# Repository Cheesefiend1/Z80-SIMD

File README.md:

# Z80-SIMD

The first (maybe only ever) SIMD z80 computer.
Software will be written soon

Schematics in PDF form are available aswell in kicad schematic form.

Go nuts!

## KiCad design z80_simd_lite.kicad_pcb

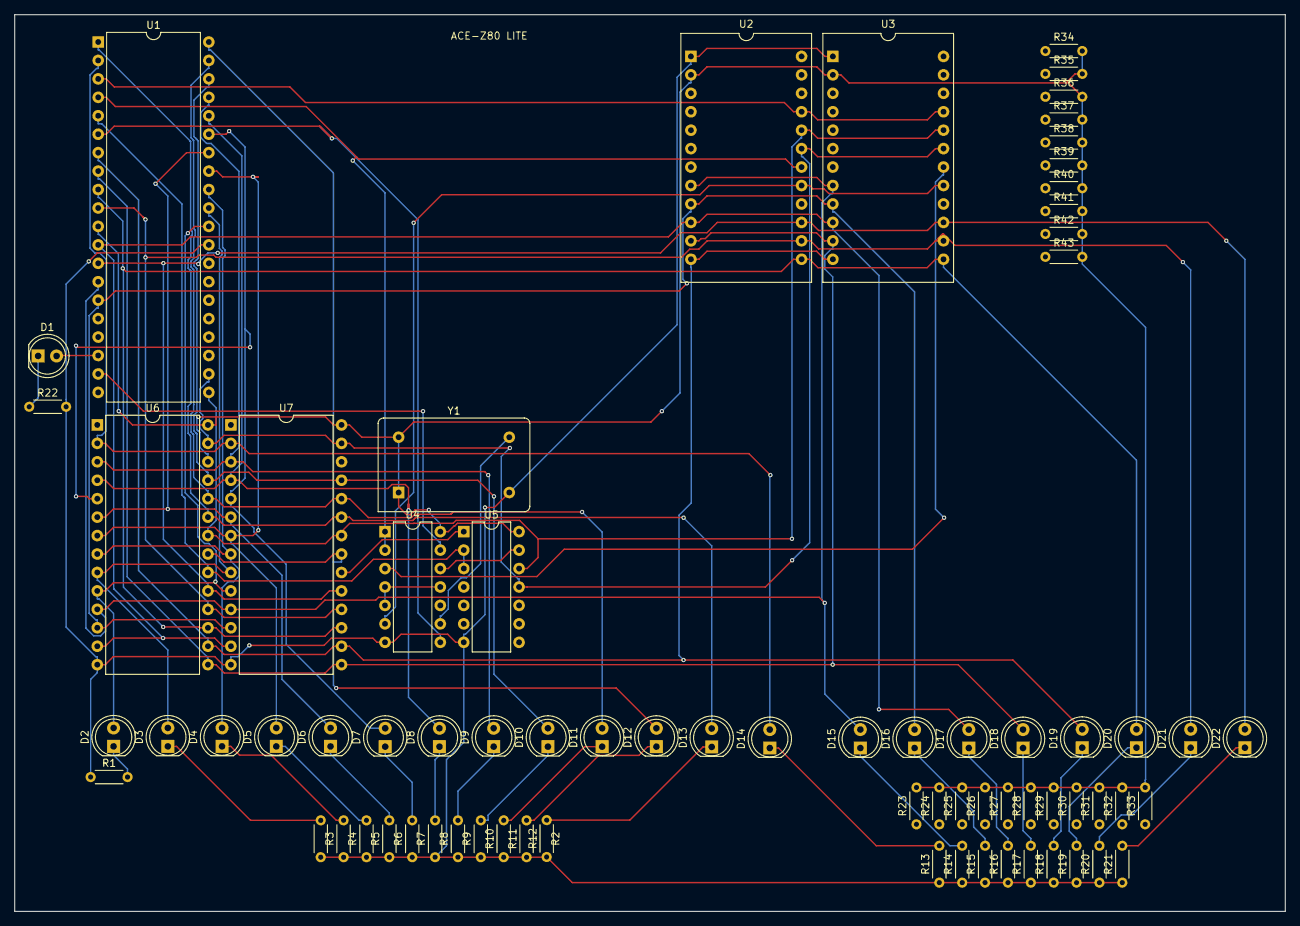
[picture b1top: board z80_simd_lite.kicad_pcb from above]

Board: 2 copper layers, 175.0 x 123.5 mm, 73 parts (0 on the bottom side), 59 nets.

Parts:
D1, D2, D3, D4, D5, D6, D7, D8, D9, D10, D11, D12, D13, D14, D15, D16, D17, D18, D19, D20, D21, D22: LED; LED_D5.0mm
R1, R2, R3, R4, R5, R6, R7, R8, R9, R10, R11, R12, R13, R14, R15, R16, R17, R18, R19, R20, R21, R22, R23, R24, R25, R26, R27, R28, R29, R30, R31, R32, R33, R34, R35, R36, R37, R38, R39, R40, R41, R42, R43: R; R_Axial_DIN0204_L3.6mm_D1.6mm_P5.08mm_Horizontal
U1: Z80CPU; DIP-40_W15.24mm
U2, U3: DIP-24_18.0mmx34.29mm_W15.24mm
U4: 74LS00; DIP-14_W7.62mm
U5: 7402; DIP-14_W7.62mm
U6: HY6264AxP; DIP-28_W15.24mm
U7: KM28C64A; DIP-28_W15.24mm
Y1: CXO_DIP14; Oscillator_DIP-14

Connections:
/A0: D2.2 (A), U1.30 (A0), U6.10 (A0), U7.10 (A0)
/A1: D3.2 (A), U1.31 (A1), U6.9 (A1), U7.9 (A1)
/A2: D4.2 (A), U1.32 (A2), U6.8 (A2), U7.8 (A2)
/A3: D5.2 (A), U1.33 (A3), U6.7 (A3), U7.7 (A3)
/A4: D6.2 (A), U1.34 (A4), U6.6 (A4), U7.6 (A4)
/A5: D7.2 (A), U1.35 (A5), U6.5 (A5), U7.5 (A5)
/A6: D8.2 (A), U1.36 (A6), U6.4 (A6), U7.4 (A6)
/A7: D9.2 (A), U1.37 (A7), U6.3 (A7), U7.3 (A7)
/A8: D10.2 (A), U1.38 (A8), U6.25 (A8), U7.25 (A8)
/A9: D11.2 (A), U1.39 (A9), U6.24 (A9), U7.24 (A9)
/A10: D12.2 (A), U1.40 (A10), U6.21 (A10), U7.21 (A10)
/A11: D13.2 (A), U1.1 (A11), U6.23 (A11), U7.23 (A11)
/A12: D14.2 (A), U1.2 (A12), U6.2 (A12), U7.2 (A12)
/D0: D15.2 (A), U1.14 (D0), U2.8 (DB0), U3.8 (DB0), U6.11 (I/O0), U7.11 (I/O0)
/D1: D16.2 (A), U1.15 (D1), U2.9 (DB1), U3.9 (DB1), U6.12 (I/O1), U7.12 (I/O1)
/D2: D17.2 (A), U1.12 (D2), U2.10 (DB2), U3.10 (DB2), U6.13 (I/O2), U7.13 (I/O2)
/D3: D18.2 (A), U1.8 (D3), U2.11 (DB3), U3.11 (DB3), U6.15 (I/O3), U7.15 (I/O3)
/D4: D19.2 (A), U1.7 (D4), U2.12 (DB4), U3.12 (DB4), U6.16 (I/O4), U7.16 (I/O4)
/D5: D20.2 (A), U1.9 (D5), U2.13 (DB5), U3.13 (DB5), U6.17 (I/O5), U7.17 (I/O5)
/D6: D21.2 (A), U1.10 (D6), U2.14 (DB6), U3.14 (DB6), U6.18 (I/O6), U7.18 (I/O6)
/D7: D22.2 (A), U1.13 (D7), U2.15 (DB7), U3.15 (DB7), U6.19 (I/O7), U7.19 (I/O7)
unnamed: D1.2 (A), U1.18 (~HALT)
unnamed: D1.1 (K), R22.1
unnamed: D2.1 (K), R1.2
unnamed: D3.1 (K), R2.2
unnamed: D4.1 (K), R3.2
unnamed: D5.1 (K), R4.2
unnamed: D6.1 (K), R5.2
unnamed: D7.1 (K), R6.2
unnamed: D8.1 (K), R7.2
unnamed: D9.1 (K), R8.2
unnamed: D10.1 (K), R9.2
unnamed: D11.1 (K), R10.2
unnamed: D12.1 (K), R11.2
unnamed: D13.1 (K), R12.2
unnamed: D14.1 (K), R13.2
unnamed: D15.1 (K), R14.2
unnamed: D16.1 (K), R15.2
unnamed: D17.1 (K), R16.2
unnamed: D18.1 (K), R17.2
unnamed: D19.1 (K), R18.2
unnamed: D20.1 (K), R19.2
unnamed: D21.1 (K), R20.2
unnamed: D22.1 (K), R21.2
unnamed: U1.3 (A13), U2.21 (C/D), U3.21 (C/D)
unnamed: U1.4 (A14), U2.18 (CS), U4.1, U4.2
unnamed: U1.5 (A15), U5.2, U5.3, U6.20 (~CS1)
unnamed: R1.1, R2.1, R3.1, R4.1, R5.1, R6.1, R7.1, R8.1, R9.1, R10.1, R11.1, R12.1, R13.1, R14.1, R15.1, R16.1, R17.1, R18.1, R19.1, R20.1, R21.1, R22.2, U1.29 (GND), U2.1 (VSS), U3.1 (VSS), U4.7 (GND), U5.7 (GND), U6.14 (GND), U7.14 (GND), Y1.7 (GND)
unnamed: R23.2, R24.2, R25.2, R26.2, R27.2, R28.2, R29.2, R30.2, R31.2, R32.2, R33.2, R34.2, R35.2, R36.2, R37.2, R38.2, R39.2, R40.2, R41.2, R42.2, R43.2, U1.11 (VCC), U2.2 (VCC+5V), U3.2 (VCC+5V), U4.14 (VCC), U5.14 (VCC), U6.26 (CS2), U6.28 (VCC), U7.28 (VCC), Y1.1 (EN), Y1.14 (Vcc)
unnamed: U1.6 (~CLK), U4.8
unnamed: U1.19 (~MREQ), U4.13
unnamed: U1.21 (~RD), U2.20 (RD), U3.20 (RD), U5.12, U6.22 (~OE), U7.22 (~OE)
unnamed: U1.22 (~WR), U2.19 (WR), U3.19 (WR), U5.11, U6.27 (~WE), U7.27 (~WE)
unnamed: U2.17 (PAUSE), U3.17 (PAUSE), U4.6
unnamed: U3.18 (CS), U4.3
unnamed: U4.4, U4.5, U4.11
unnamed: U4.12, U5.13
unnamed: U5.1, U7.20 (~CE)
unnamed: U4.9, Y1.8 (OUT)

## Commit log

2025-07-08 Schematic PDFS
